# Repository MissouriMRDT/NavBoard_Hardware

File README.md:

# MRDT NavBoard Hardware

## Purpose
The Navigation (Nav) Board is responsible for containing, supplying, and interfacing the equipment required to determine the rover's position and orientation. This board does this by utilizing 2 inertial measurement units (IMUs) and a connection to an external GPS receiver. This data is processed and sent to the rest of the rover via an ethernet connection.
## Design

This revision of the board is a new design, based on the components and connections from the 2022/2023 Rev 2 designs. The goal of this design was to make the board as small as possible, and to mount onto a Teensy 4.1 instead of a raspberry pi.

This design utilizes a 4-layer PCB with holes for M3 mounting screws on 15mm standoffs. The Teensy is soldered onto one side of the board, and all of the smd components are mounted on the other side.

This design also includes an ethernet RJ45 jack for allowing ethernet connectivity to the Teensy.

## Required External Connections
 - +12V
 - GPS (I2C and UART)
 - Teensy 4.1
 - Ethernet

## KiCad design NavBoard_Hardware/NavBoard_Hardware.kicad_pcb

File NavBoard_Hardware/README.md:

# MRDT NavBoard PCB

## Dimensions
 - 100mm Long (124.29mm w/ Horizontal Power Poles)
 - 33.1mm Wide
## Board Specifications

 - 4-layer
  -- Top Copper (Signals, SMD Components, Ground Pour)
  -- Ground Copper
  -- Power Copper (3V3, 5V, 12V)
  -- Bottom Copper (Signals, Ethernet, Ground Pour)
 - 1-oz Copper
 - 1.6mm Thick
## Mounting Points
This module is designed as a daughter board to be mounted on top of a Teensy 4.1 microcontroller. There are holes at each corner of the board for mounting M3 standoffs. These holes are electrically connected to ground.

The powerpole connectors can be mounted vertically to reduce horizontal space.

The Teensy 4.1 needs to be mounted with the USB port facing the Ethernet port.

The Teensy 4.1 also needs to be mounted so that its reset button is accessible.

The MicroSD card should be accessible if the PowerPole connectors do not extend below the holes too much.

The Teensy 4.1 ethernet pins are 2.00mm pitch, NOT the standard 2.54mm. These also will likely need to be longer than standard 2.00mm pins, as 2.00 pins are shorter in length an 2.54mm pins.

The Teensy 4.1 CAN be socketed onto the PCB, but it is recommended for structural integrity reasons that it be direcly soldered into place using 2.54mm and 2.00mm pins.

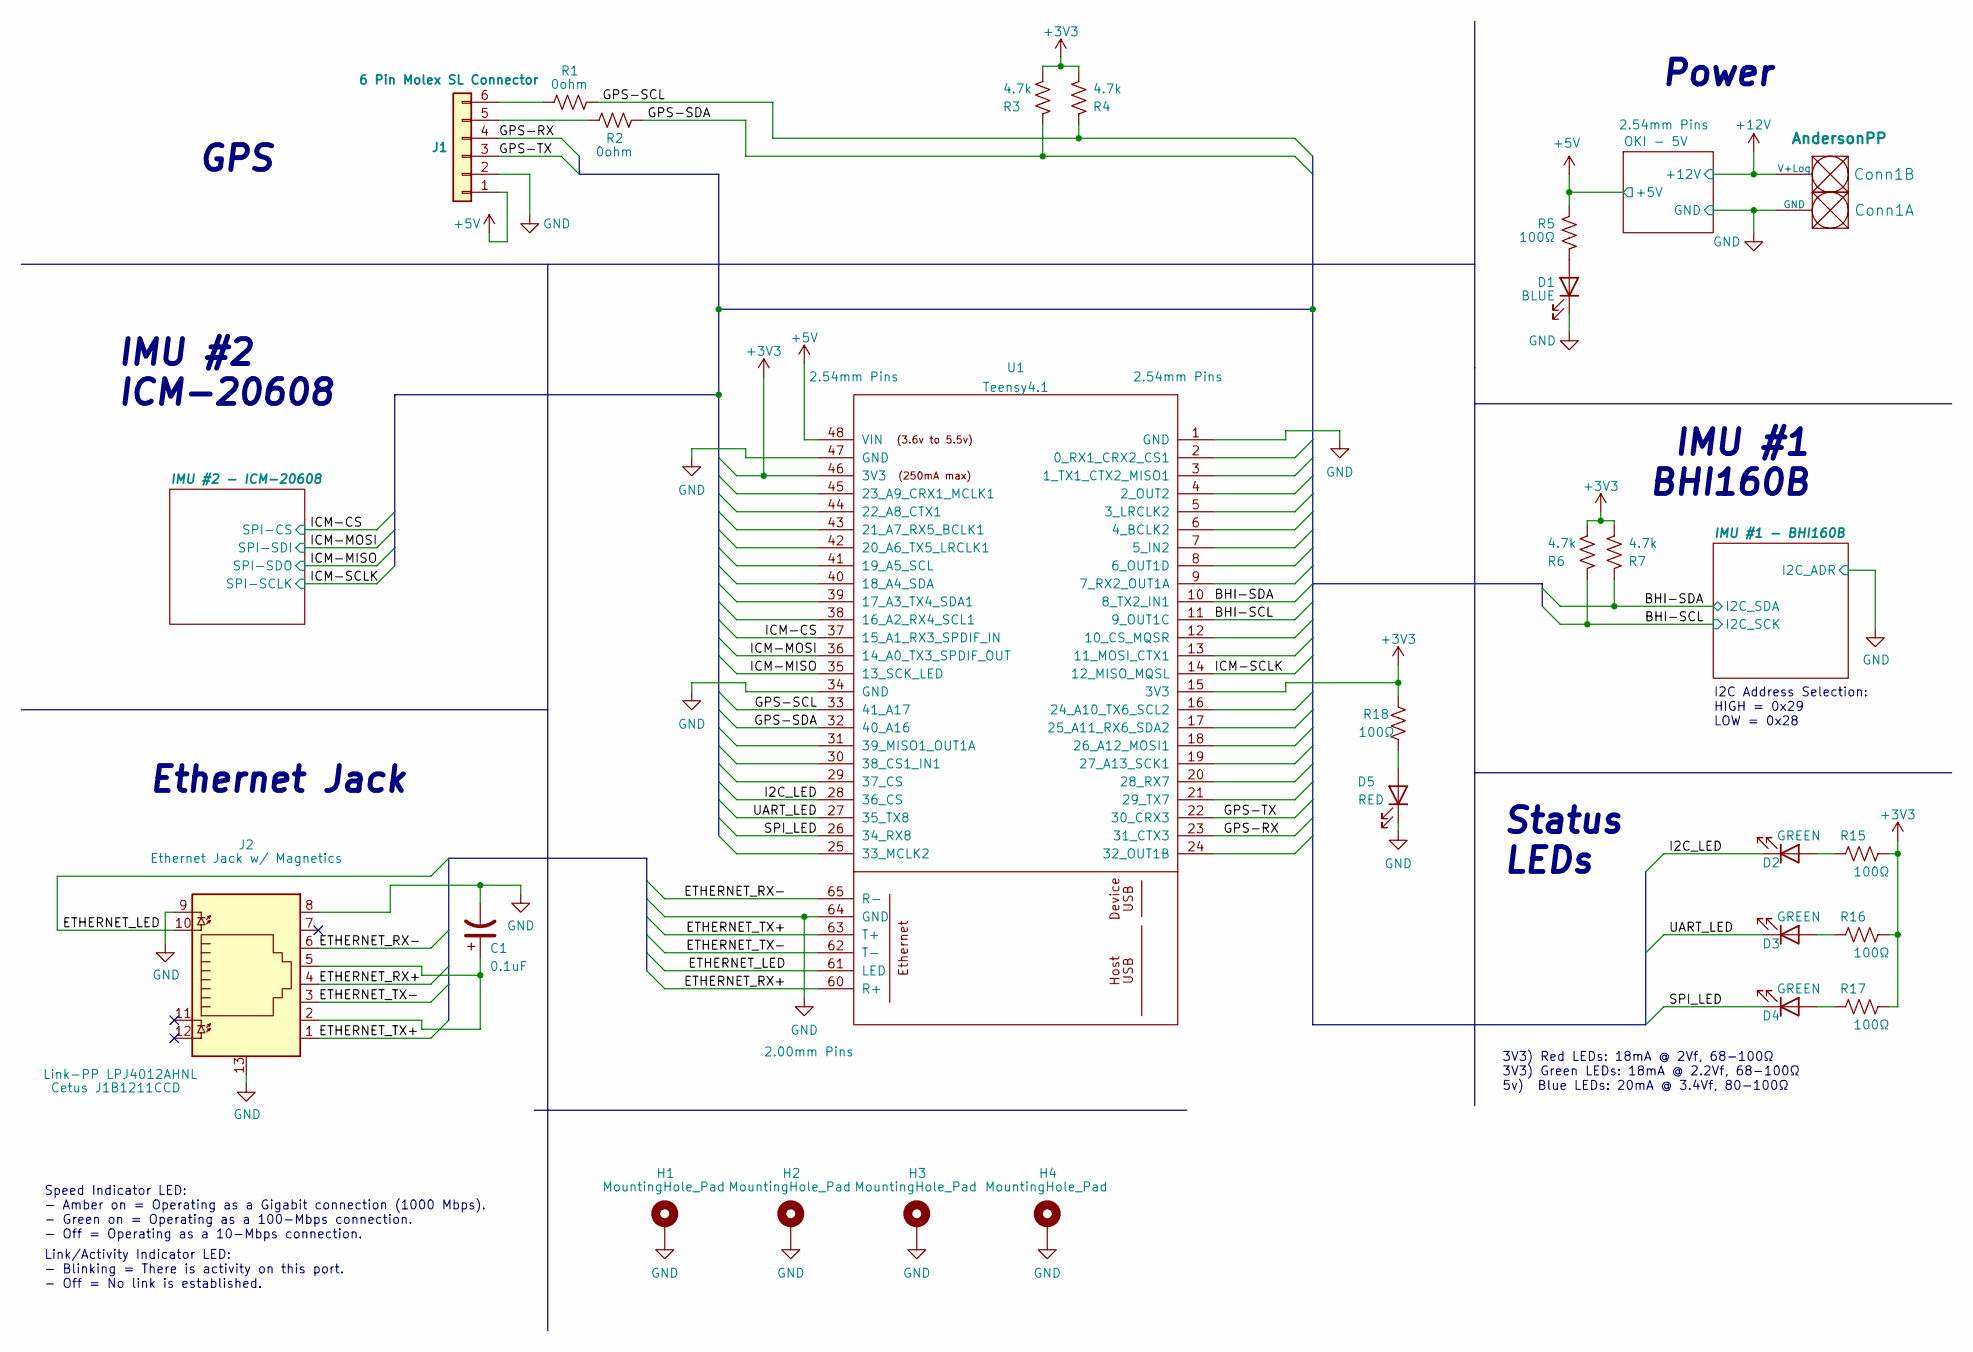
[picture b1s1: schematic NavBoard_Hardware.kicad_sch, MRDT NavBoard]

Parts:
C1: 0.1uF; C_0603_1608Metric_Pad1.08x0.95mm_HandSolder
Conn1: AndersonPP; Square_Anderson_2_H_Side_By_Side
D1: BLUE; LED_0603_1608Metric_Pad1.05x0.95mm_HandSolder
D2, D3, D4: GREEN; LED_0603_1608Metric_Pad1.05x0.95mm_HandSolder
D5: RED; LED_0603_1608Metric_Pad1.05x0.95mm_HandSolder
H1, H2, H3, H4: MountingHole_Pad
J1: 6 Pin Molex SL Connector; MOLEX_SL_06_Vertical
J2: Ethernet Jack w/ Magnetics; RJ45_Cetus_J1B1211CCD_Horizontal; Part Opt 1 Link-PP LPJ4012AHNL
R1, R2: 0ohm; R_0603_1608Metric_Pad0.98x0.95mm_HandSolder
R3, R4, R6, R7: 4.7k; R_0603_1608Metric_Pad0.98x0.95mm_HandSolder
R5, R15, R16, R17, R18: 100Ω; R_0603_1608Metric_Pad0.98x0.95mm_HandSolder
U1: Teensy4.1; Teensy41

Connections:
+5V: J1.1, R5.1, U1.48 (VIN); also elsewhere on the board
+12V: Conn1.2 (V+Log); also elsewhere on the board
/BHI-SCL: R6.1, U1.11 (9_OUT1C); also elsewhere on the board
/BHI-SDA: R7.1, U1.10 (8_TX2_IN1); also elsewhere on the board
/ETHERNET_LED: J2.10, U1.61 (LED)
/ETHERNET_RX+: J2.4, U1.60 (R+)
/ETHERNET_RX-: J2.6, U1.65 (R-)
/ETHERNET_TX+: J2.1, U1.63 (T+)
/ETHERNET_TX-: J2.3, U1.62 (T-)
/GPS-RX: J1.4, U1.23 (31_CTX3)
/GPS-SCL: R1.2, R4.1, U1.33 (41_A17)
/GPS-SDA: R2.2, R3.1, U1.32 (40_A16)
/GPS-TX: J1.3, U1.22 (30_CRX3)
/I2C_LED: D2.1 (K), U1.28 (36_CS)
/ICM-CS: U1.37 (15_A1_RX3_SPDIF_IN); also elsewhere on the board
/ICM-MISO: U1.35 (13_SCK_LED); also elsewhere on the board
/ICM-MOSI: U1.36 (14_A0_TX3_SPDIF_OUT); also elsewhere on the board
/ICM-SCLK: U1.14 (12_MISO_MQSL); also elsewhere on the board
/SPI_LED: D4.1 (K), U1.26 (34_RX8)
/UART_LED: D3.1 (K), U1.27 (35_TX8)
GND: C1.2, Conn1.1 (GND), D1.1 (K), D5.1 (K), H1.1, H2.1, H3.1, H4.1, J1.2, J2.8, J2.9, J2.13, U1.1 (GND), U1.34 (GND), U1.47 (GND), U1.64 (GND); also elsewhere on the board
unnamed: C1.1, J2.2, J2.5
unnamed: D1.2 (A), R5.2
unnamed: D2.2 (A), R15.2
unnamed: D3.2 (A), R16.2
unnamed: D4.2 (A), R17.2
unnamed: D5.2 (A), R18.2
unnamed: J1.5, R2.1
unnamed: J1.6, R1.1

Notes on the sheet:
Link/Activity Indicator LED: - Blinking = There is activity on this port. - Off = No link is established.
GPS
I2C Address Selection: HIGH = 0x29 LOW = 0x28
IMU #1 BHI160B
Status LEDs
IMU #2 ICM-20608
Speed Indicator LED: - Amber on = Operating as a Gigabit connection (1000 Mbps). - Green on = Operating as a 100-Mbps connection. - Off = Operating as a 10-Mbps connection.
Ethernet Jack
Power
3V3) Red LEDs: 18mA @ 2Vf, 68-100Ω 3V3) Green LEDs: 18mA @ 2.2Vf, 68-100Ω 5v) Blue LEDs: 20mA @ 3.4Vf, 80-100Ω

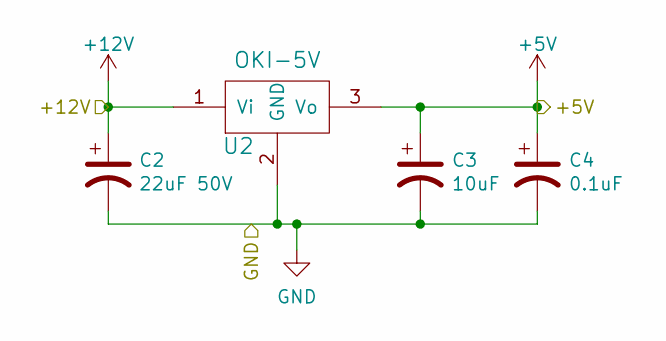
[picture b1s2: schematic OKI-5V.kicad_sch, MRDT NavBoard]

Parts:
C2: 22uF 50V; C_1206_3216Metric_Pad1.33x1.80mm_HandSolder
C3: 10uF; C_0603_1608Metric_Pad1.08x0.95mm_HandSolder
C4: 0.1uF; C_0603_1608Metric_Pad1.08x0.95mm_HandSolder
U2: OKI-5V; OKI_Vertical_TSR

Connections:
+5V: C3.1, C4.1, U2.3 (Vo); also elsewhere on the board
+12V: C2.1, U2.1 (Vi); also elsewhere on the board
GND: C2.2, C3.2, C4.2, U2.2 (GND); also elsewhere on the board

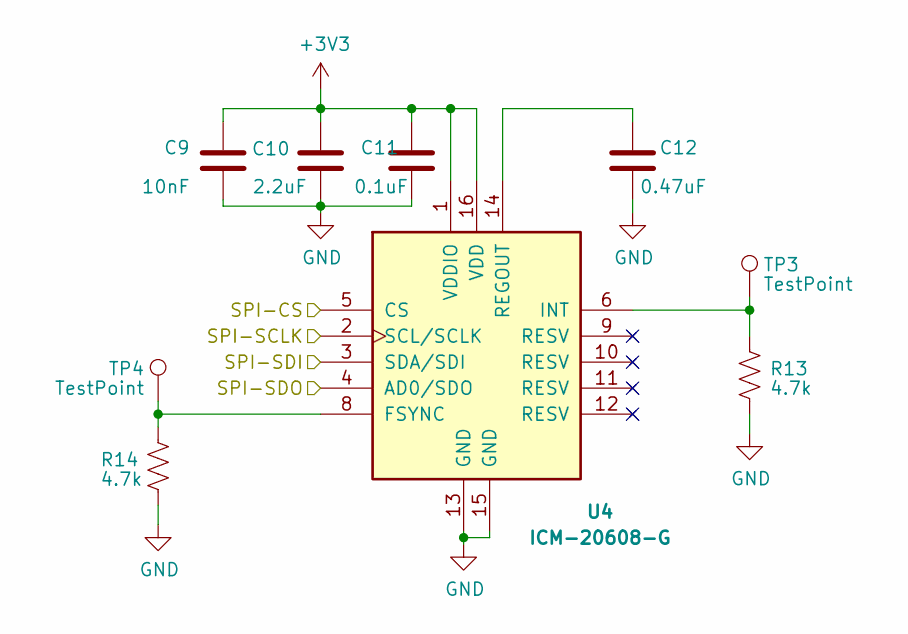
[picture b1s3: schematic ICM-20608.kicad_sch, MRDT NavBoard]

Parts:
C9: 10nF; C_0603_1608Metric_Pad1.08x0.95mm_HandSolder
C10: 2.2uF; C_0603_1608Metric_Pad1.08x0.95mm_HandSolder
C11: 0.1uF; C_0603_1608Metric_Pad1.08x0.95mm_HandSolder
C12: 0.47uF; C_0603_1608Metric_Pad1.08x0.95mm_HandSolder
R13, R14: 4.7k; R_0603_1608Metric_Pad0.98x0.95mm_HandSolder
TP3, TP4: TestPoint; TestPoint_Pad_D1.5mm
U4: ICM-20608-G; ICM-20608-G_ExtendedPads; PARTREV 1.0

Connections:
/ICM-CS: U4.5 (CS); also elsewhere on the board
/ICM-MISO: U4.4 (AD0/SDO); also elsewhere on the board
/ICM-MOSI: U4.3 (SDA/SDI); also elsewhere on the board
/ICM-SCLK: U4.2 (SCL/SCLK); also elsewhere on the board
GND: C9.2, C10.2, C11.2, C12.2, R13.2, R14.2, U4.13 (GND), U4.15 (GND); also elsewhere on the board
unnamed: C12.1, U4.14 (REGOUT)
unnamed: R13.1, TP3.1, U4.6 (INT)
unnamed: R14.1, TP4.1, U4.8 (FSYNC)

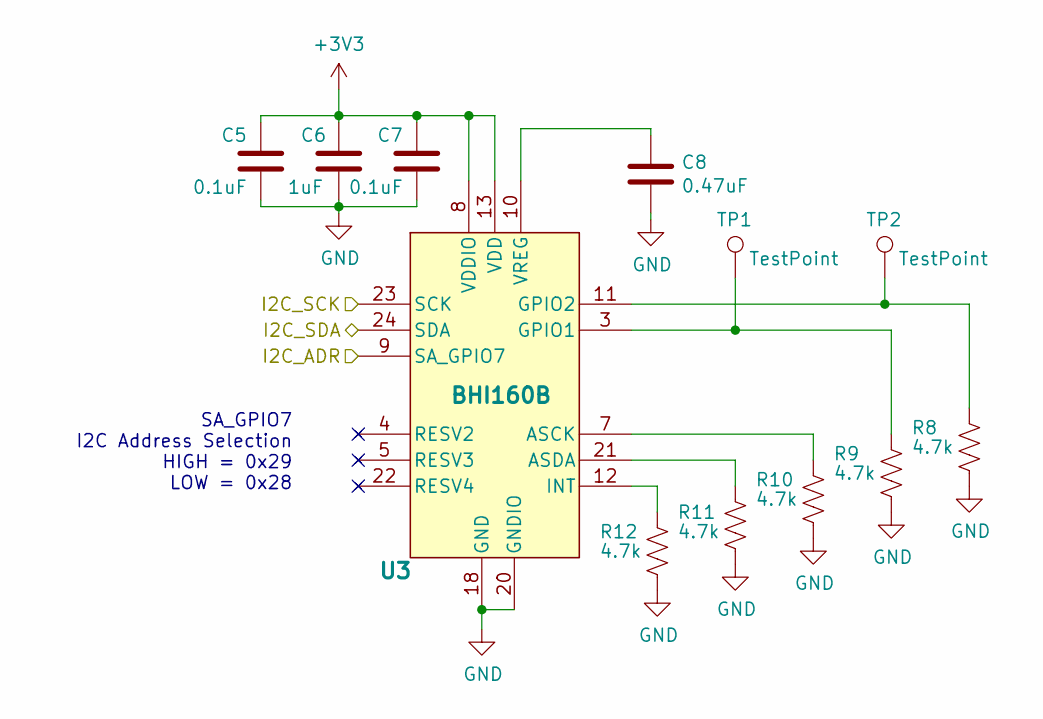
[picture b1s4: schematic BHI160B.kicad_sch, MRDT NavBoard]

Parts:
C5, C7: 0.1uF; C_0603_1608Metric_Pad1.08x0.95mm_HandSolder
C6: 1uF; C_0603_1608Metric_Pad1.08x0.95mm_HandSolder
C8: 0.47uF; C_0603_1608Metric_Pad1.08x0.95mm_HandSolder
R8, R9, R10, R11, R12: 4.7k; R_0603_1608Metric_Pad0.98x0.95mm_HandSolder
TP1, TP2: TestPoint; TestPoint_Pad_D1.5mm
U3: BHI160B; BHI160B_ExtendedPads

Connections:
/BHI-SCL: U3.23 (SCK); also elsewhere on the board
/BHI-SDA: U3.24 (SDA); also elsewhere on the board
GND: C5.2, C6.2, C7.2, C8.2, R8.2, R9.2, R10.2, R11.2, R12.2, U3.9 (SA_GPIO7), U3.18 (GND), U3.20 (GNDIO); also elsewhere on the board
unnamed: C8.1, U3.10 (VREG)
unnamed: R8.1, TP2.1, U3.11 (GPIO2)
unnamed: R9.1, TP1.1, U3.3 (GPIO1)
unnamed: R10.1, U3.7 (ASCK)
unnamed: R11.1, U3.21 (ASDA)
unnamed: R12.1, U3.12 (INT)

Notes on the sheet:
SA_GPIO7 I2C Address Selection HIGH = 0x29 LOW = 0x28

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
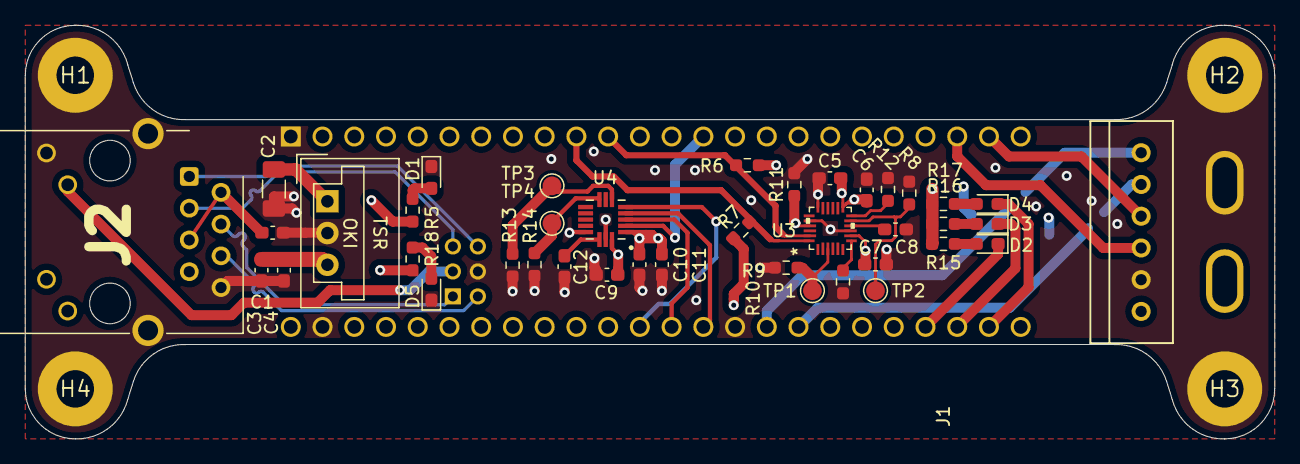
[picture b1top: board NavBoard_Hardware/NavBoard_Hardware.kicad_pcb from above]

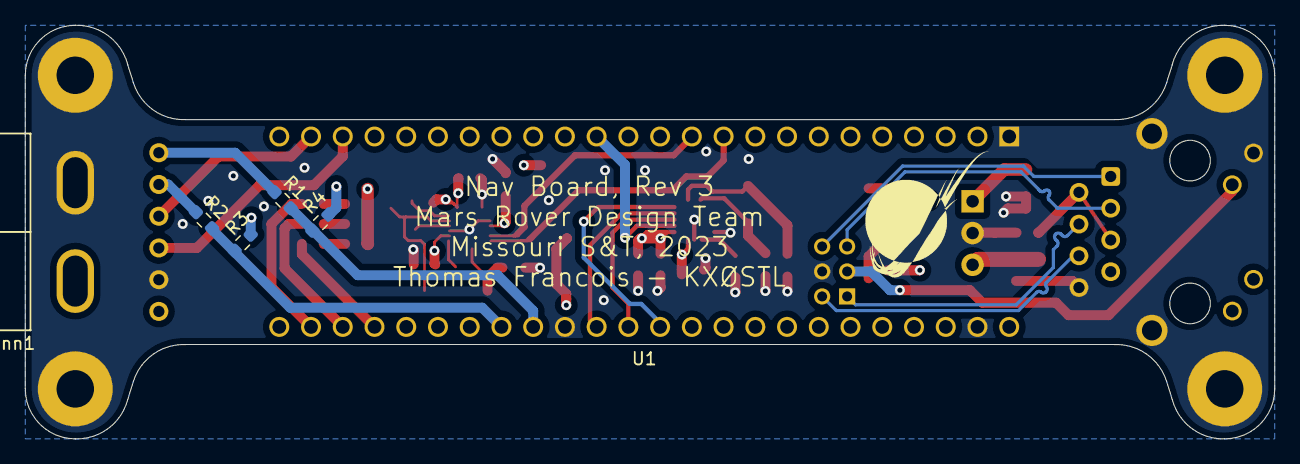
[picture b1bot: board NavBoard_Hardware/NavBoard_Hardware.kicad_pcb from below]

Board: 4 copper layers, 100.0 x 33.1 mm, 50 parts (6 on the bottom side), 39 nets.

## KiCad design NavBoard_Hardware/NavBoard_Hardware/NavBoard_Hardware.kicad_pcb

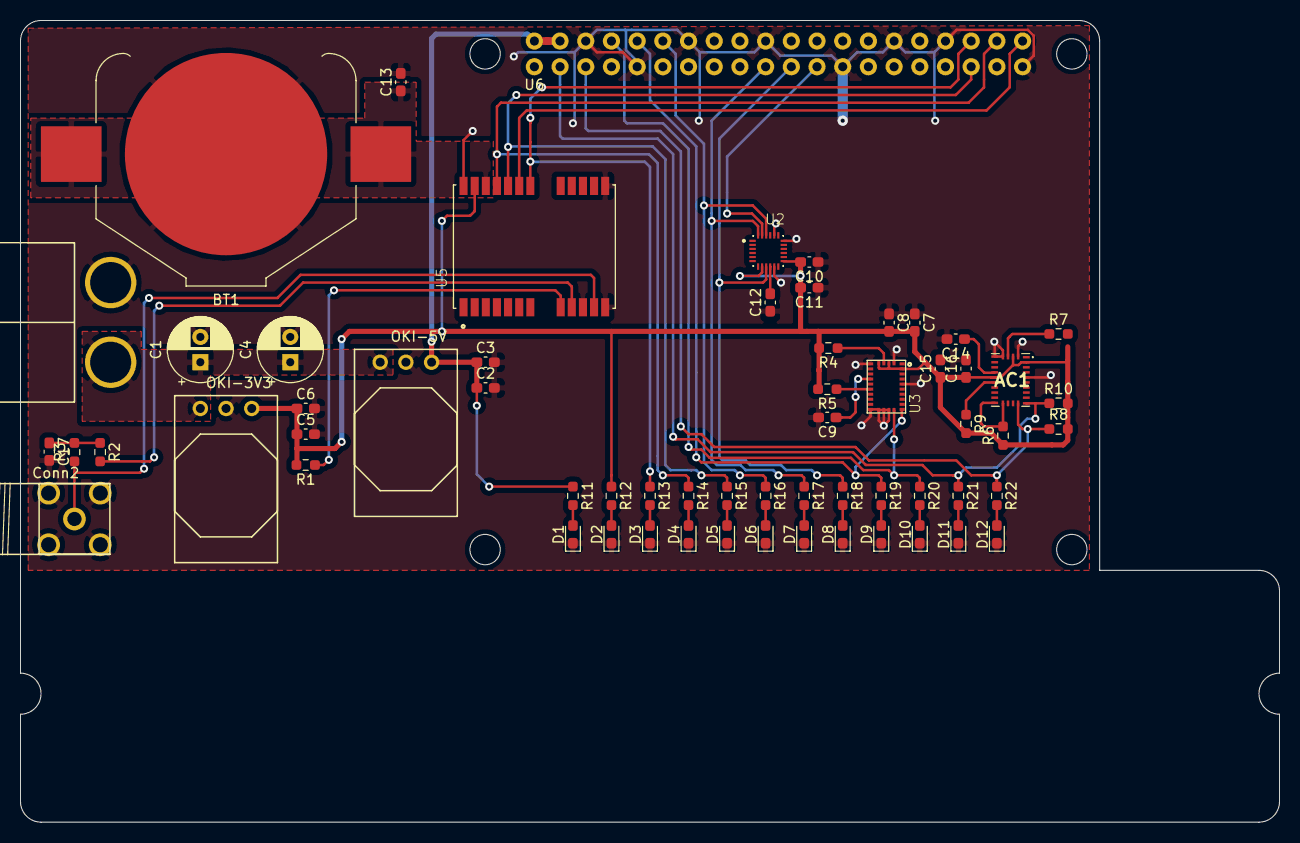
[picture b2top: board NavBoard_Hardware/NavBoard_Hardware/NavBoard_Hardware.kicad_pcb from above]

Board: 2 copper layers, 124.5 x 79.2 mm, 61 parts (0 on the bottom side), 41 nets.

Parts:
AC1: BNO080
BT1: Battery_Cell; BatteryHolder_Keystone_3008_1x2450
C1, C4: 22uF 50V; CP_Radial_D6.3mm_P2.50mm
C2, C5: 10uF; C_0603_1608Metric_Pad1.08x0.95mm_HandSolder
C3, C6, C9, C10, C11, C12, C14, C15, C16: 0.1uF; C_0603_1608Metric_Pad1.08x0.95mm_HandSolder
C7: 6.8nF; C_0603_1608Metric_Pad1.08x0.95mm_HandSolder
C8: 120nF; C_0603_1608Metric_Pad1.08x0.95mm_HandSolder
C13: 1uF; C_0603_1608Metric_Pad1.08x0.95mm_HandSolder
C17: 47pF; C_0603_1608Metric_Pad1.08x0.95mm_HandSolder
Conn1: AndersonPP; Anderson_2_Horizontal_Side_by_Side
Conn2: RP-SMA; RP-SMA_Jack_Tru-Hole_Right-Angle
D1, D2: GREEN; LED_0603_1608Metric_Pad1.05x0.95mm_HandSolder
D3, D4, D5, D6, D7, D8, D9, D10, D11, D12: BLUE; LED_0603_1608Metric_Pad1.05x0.95mm_HandSolder
R1: 10K; R_0603_1608Metric_Pad0.98x0.95mm_HandSolder
R2: 10; R_0603_1608Metric_Pad0.98x0.95mm_HandSolder
R3: 30@100MHZ/2.0A; R_0603_1608Metric_Pad0.98x0.95mm_HandSolder
R4, R5, R7, R9: 10k; R_0603_1608Metric_Pad0.98x0.95mm_HandSolder
R6, R8, R10: 2.2k; R_0603_1608Metric_Pad0.98x0.95mm_HandSolder
R11, R13, R14, R15, R16, R17, R18, R19, R20, R21, R22: 100; R_0603_1608Metric_Pad0.98x0.95mm_HandSolder
R12: 43; R_0603_1608Metric_Pad0.98x0.95mm_HandSolder
U1: OKI-5V; OKI_Horizontal
U2: ICM-20948; ICM_20948
U3: BNO055
U4: OKI-3V3; OKI_Horizontal
U5: NEO-M8P-2; MODULE_NEO-M8P-2
U6: Raspberry_Pi; RaspberryPi_THT_BOTTOM

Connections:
+3V3: AC1.3, AC1.10, AC1.28, C5.1, C6.1, C7.2, C8.2, C10.2, C11.2, C15.1, C16.1, R1.2, R4.2, R5.2, R6.1, R7.2, R8.2, R9.2, R10.2, R12.1, U2.8, U2.13, U3.3, U3.5, U3.28, U4.3, U5.23
+5V: C2.1, C3.1, R11.1, U1.3, U6.2, U6.4
+12V: C1.1, C4.1, Conn1.2, U1.1, U4.1
BNO055_RX: R20.1, U3.19, U6.8
BNO055_TX: R19.1, U3.20, U6.10
BNO080_SCL: AC1.19, R8.1, R22.1, U6.5
BNO080_SDA: AC1.20, R10.1, R21.1, U6.3
GND: AC1.2, AC1.5, AC1.6, AC1.25, BT1.2, C1.2, C2.2, C3.2, C4.2, C5.2, C6.2, C7.1, C8.1, C9.2, C10.1, C11.1, C12.1, C13.2, C14.2, C15.2, C16.2, C17.2, Conn1.1, Conn2.2, D1.1, D2.1, D3.1, D4.1, D5.1, D6.1, D7.1, D8.1, D9.1, D10.1, D11.1, D12.1, U1.2, U2.11, U2.18, U2.20, U3.2, U3.6, U3.15, U3.16, U3.17, U3.18, U3.25, U4.2, U5.2, U5.10, U5.12, U5.13, U5.24, U6.6, U6.9, U6.14, U6.20, U6.25, U6.30, U6.34, U6.39
ICM_CS: R16.1, U2.22, U6.12
ICM_MISO: R18.1, U2.9, U6.21
ICM_MOSI: R17.1, U2.24, U6.19
ICM_SCLK: U2.23, U6.23
M8P_CLK: U5.19, U6.40
M8P_CS: R13.1, U5.18, U6.36
M8P_MISO: R15.1, U5.20, U6.35
M8P_MOSI: R14.1, U5.21, U6.38
unnamed: AC1.4, R7.1
unnamed: AC1.9, C14.1
unnamed: AC1.11, R9.1
unnamed: AC1.15, AC1.16, R6.2
unnamed: C9.1, U3.9
unnamed: C12.2, U2.10
unnamed: C17.1, R2.1, R3.2
unnamed: Conn2.1, R3.1, U5.11
unnamed: D1.2, R11.2
unnamed: D2.2, R12.2
unnamed: D3.2, R13.2
unnamed: D4.2, R14.2
unnamed: D5.2, R15.2
unnamed: D6.2, R16.2
unnamed: D7.2, R17.2
unnamed: D8.2, R18.2
unnamed: D9.2, R19.2
unnamed: D10.2, R20.2
unnamed: D11.2, R21.2
unnamed: D12.2, R22.2
unnamed: R1.1, U5.8
unnamed: R2.2, U5.9
unnamed: R4.1, U3.4
unnamed: R5.1, U3.11
V_BCKP: BT1.1, C13.1, U5.22

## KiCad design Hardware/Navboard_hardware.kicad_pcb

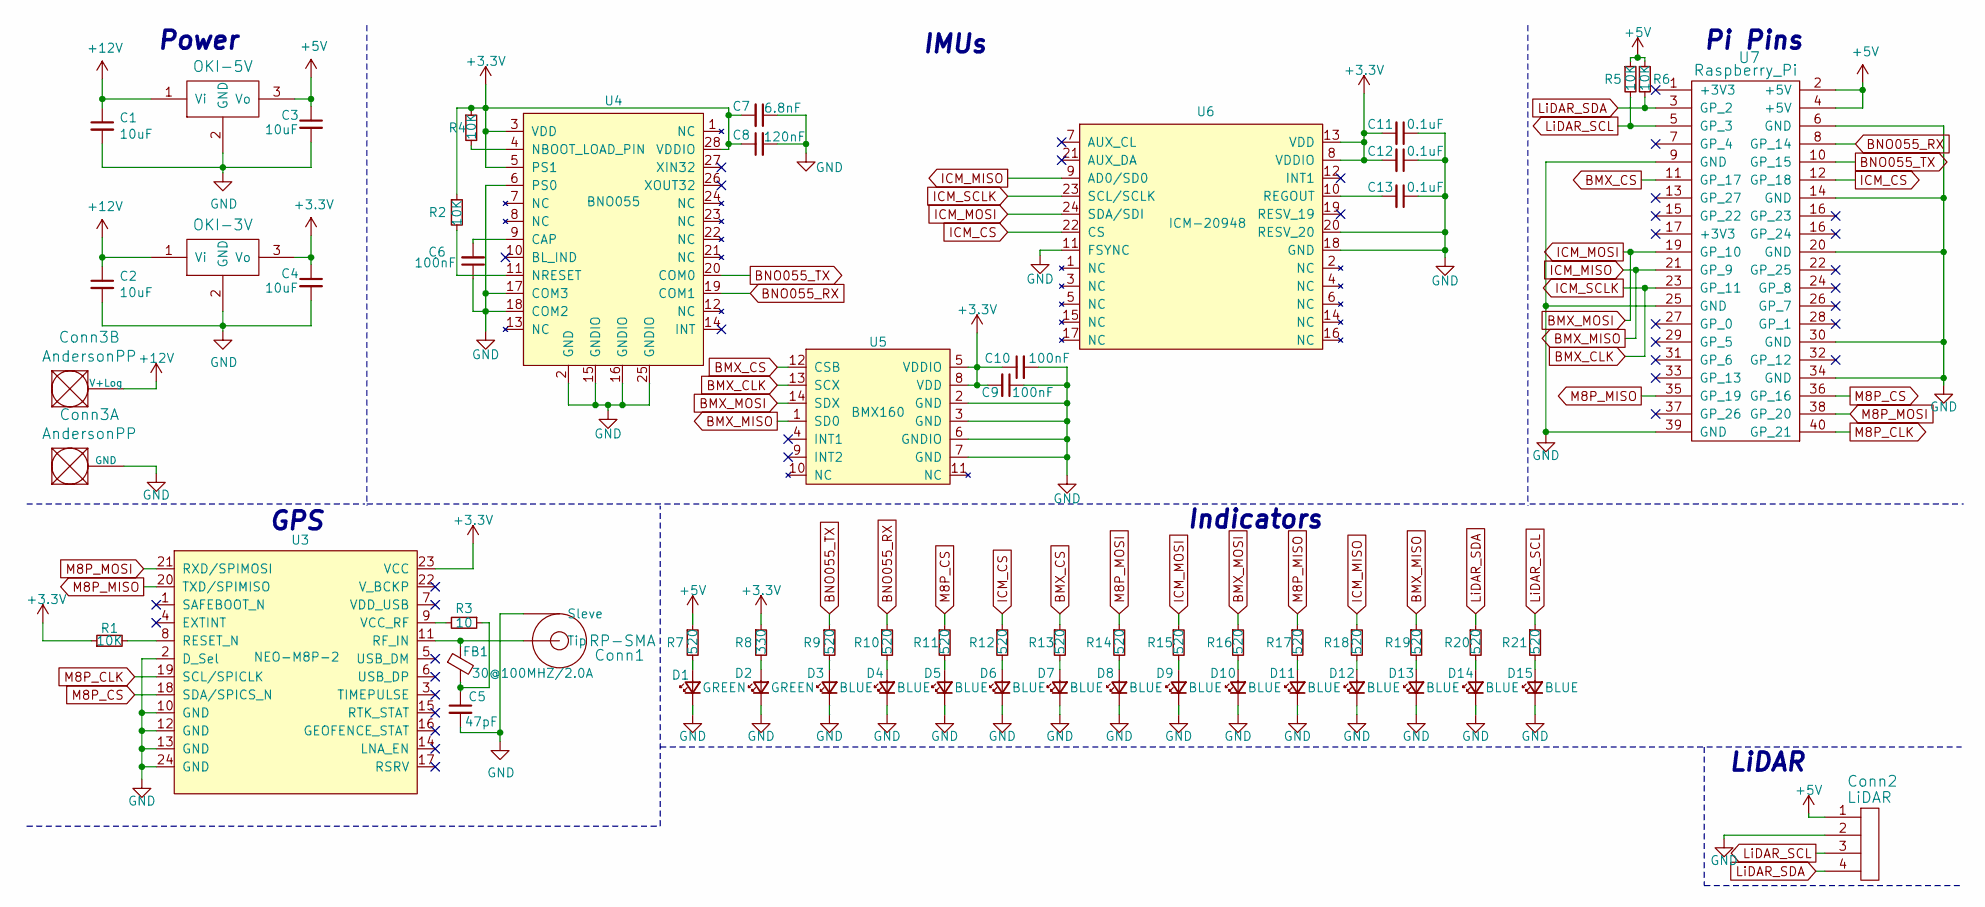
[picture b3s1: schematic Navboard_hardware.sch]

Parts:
C1, C2, C3, C4: 10uF; C_0603_1608Metric_Pad1.08x0.95mm_HandSolder
C5: 47pF; C_0603_1608Metric_Pad1.08x0.95mm_HandSolder
C6, C9, C10: 100nF; C_0603_1608Metric_Pad1.08x0.95mm_HandSolder
C7: 6.8nF; C_0603_1608Metric_Pad1.08x0.95mm_HandSolder
C8: 120nF; C_0603_1608Metric_Pad1.08x0.95mm_HandSolder
C11, C12, C13: 0.1uF; C_0603_1608Metric_Pad1.08x0.95mm_HandSolder
Conn1: RP-SMA; RP-SMA_Jack_Tru-Hole_Right-Angle
Conn2: LiDAR; MOLEX_SL_04_Horizontal
Conn3: AndersonPP; Anderson_2_Horizontal_Side_by_Side
D1, D2: GREEN; LED_0603_1608Metric_Pad1.05x0.95mm_HandSolder
D3, D4, D5, D6, D7, D8, D9, D10, D11, D12, D13, D14, D15: BLUE; LED_0603_1608Metric_Pad1.05x0.95mm_HandSolder
FB1: 30@100MHZ/2.0A; R_0603_1608Metric_Pad0.98x0.95mm_HandSolder
R1, R2, R4, R5, R6: 10K; R_0603_1608Metric_Pad0.98x0.95mm_HandSolder
R3: 10; R_0603_1608Metric_Pad0.98x0.95mm_HandSolder
R7, R9, R10, R11, R12, R13, R14, R15, R16, R17, R18, R19, R20, R21: 520; R_0603_1608Metric_Pad0.98x0.95mm_HandSolder
R8: 330; R_0603_1608Metric_Pad0.98x0.95mm_HandSolder
U1: OKI-5V; OKI_Horizontal
U2: OKI-3V; OKI_Horizontal
U3: NEO-M8P-2; MODULE_NEO-M8P-2
U4: BNO055
U5: BMX160
U6: ICM-20948; ICM_20948
U7: Raspberry_Pi; RaspberryPi_THT_BOTTOM

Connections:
+3V3: C4.1, C7.2, C8.1, C9.2, C10.1, C11.2, C12.2, R1.1, R2.1, R4.1, R8.1, U2.3 (Vo), U3.23 (VCC), U4.3 (VDD), U4.5 (PS1), U4.28 (VDDIO), U5.5 (VDDIO), U5.8 (VDD), U6.8 (VDDIO), U6.13 (VDD)
+5V: C3.1, Conn2.1, R5.1, R6.1, R7.1, U1.3 (Vo), U7.2 (+5V), U7.4 (+5V)
+12V: C1.1, C2.1, Conn3.2 (V+Log), U1.1 (Vi), U2.1 (Vi)
BMX_CLK: U5.13 (SCX), U6.23 (SCL/SCLK), U7.23 (GP_11)
BMX_CS: R13.1, U5.12 (CSB), U7.11 (GP_17)
BMX_MISO: R18.1, R19.1, U5.1 (SD0), U6.9 (AD0/SD0), U7.21 (GP_9)
BMX_MOSI: R15.1, R16.1, U5.14 (SDX), U6.24 (SDA/SDI), U7.19 (GP_10)
BNO055_RX: R10.1, U4.19 (COM1), U7.8 (GP_14)
BNO055_TX: R9.1, U4.20 (COM0), U7.10 (GP_15)
GND: C1.2, C2.2, C3.2, C4.2, C5.2, C6.1, C7.1, C8.2, C9.1, C10.2, C11.1, C12.1, C13.1, Conn1.2 (Sleve), Conn2.2, Conn3.1 (GND), D1.1 (K), D2.1 (K), D3.1 (K), D4.1 (K), D5.1 (K), D6.1 (K), D7.1 (K), D8.1 (K), D9.1 (K), D10.1 (K), D11.1 (K), D12.1 (K), D13.1 (K), D14.1 (K), D15.1 (K), U1.2 (GND), U2.2 (GND), U3.2 (D_Sel), U3.10 (GND), U3.12 (GND), U3.13 (GND), U3.24 (GND), U4.2 (GND), U4.6 (PS0), U4.15 (GNDIO), U4.16 (GNDIO), U4.17 (COM3), U4.18 (COM2), U4.25 (GNDIO), U5.2 (GND), U5.3 (GND), U5.6 (GNDIO), U5.7 (GND), U6.11 (FSYNC), U6.18 (GND), U6.20 (RESV_20), U7.6 (GND), U7.9 (GND), U7.14 (GND), U7.20 (GND), U7.25 (GND), U7.30 (GND), U7.34 (GND), U7.39 (GND); also elsewhere on the board
ICM_CS: R12.1, U6.22 (CS), U7.12 (GP_18)
LiDAR_SCL: Conn2.3, R5.2, R21.1, U7.5 (GP_3)
LiDAR_SDA: Conn2.4, R6.2, R20.1, U7.3 (GP_2)
M8P_CLK: U3.19 (SCL/SPICLK), U7.40 (GP_21)
M8P_CS: R11.1, U3.18 (SDA/SPICS_N), U7.36 (GP_16)
M8P_MISO: R17.1, U3.20 (TXD/SPIMISO), U7.35 (GP_19)
M8P_MOSI: R14.1, U3.21 (RXD/SPIMOSI), U7.38 (GP_20)
unnamed: C5.1, FB1.2, R3.1
unnamed: C6.2, U4.9 (CAP)
unnamed: C13.2, U6.10 (REGOUT)
unnamed 20: Conn1.1 (Tip), FB1.1, U3.11 (RF_IN); also elsewhere on the board
unnamed: D1.2 (A), R7.2
unnamed: D2.2 (A), R8.2
unnamed: D3.2 (A), R9.2
unnamed: D4.2 (A), R10.2
unnamed: D5.2 (A), R11.2
unnamed: D6.2 (A), R12.2
unnamed: D7.2 (A), R13.2
unnamed: D8.2 (A), R14.2
unnamed: D9.2 (A), R15.2
unnamed: D10.2 (A), R16.2
unnamed: D11.2 (A), R17.2
unnamed: D12.2 (A), R18.2
unnamed: D13.2 (A), R19.2
unnamed: D14.2 (A), R20.2
unnamed: D15.2 (A), R21.2
unnamed: R1.2, U3.8 (RESET_N)
unnamed: R2.2, U4.11 (NRESET)
unnamed: R3.2, U3.9 (VCC_RF)
unnamed: R4.2, U4.4 (NBOOT_LOAD_PIN)

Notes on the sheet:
Power
IMUs
Pi Pins
GPS
LiDAR
Indicators

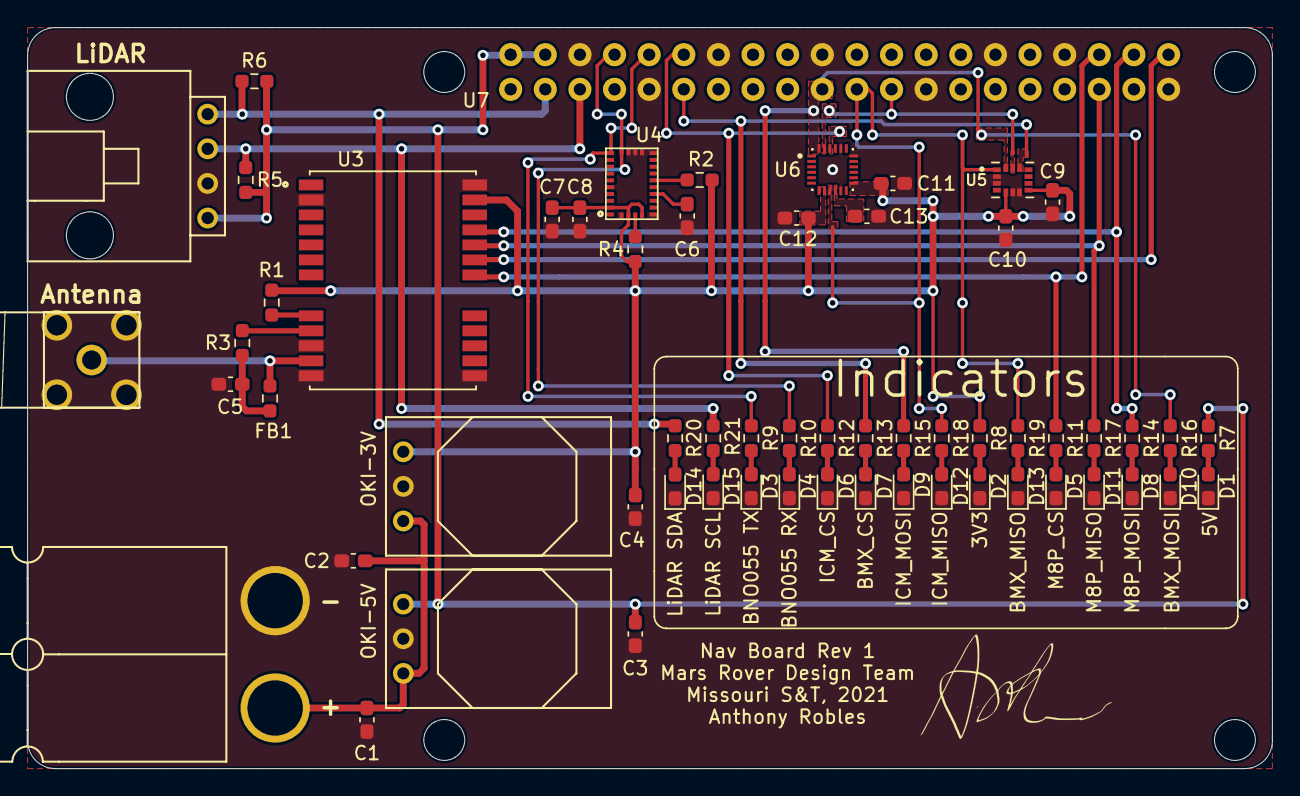
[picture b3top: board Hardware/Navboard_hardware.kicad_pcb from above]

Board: 2 copper layers, 91.3 x 54.4 mm, 60 parts (0 on the bottom side), 40 nets.

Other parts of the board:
Antenna: RP-SMA; RP-SMA_Jack_Tru-Hole_Right-Angle

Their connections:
GND: Antenna.2; also elsewhere on the board
unnamed 20: Antenna.1; also elsewhere on the board

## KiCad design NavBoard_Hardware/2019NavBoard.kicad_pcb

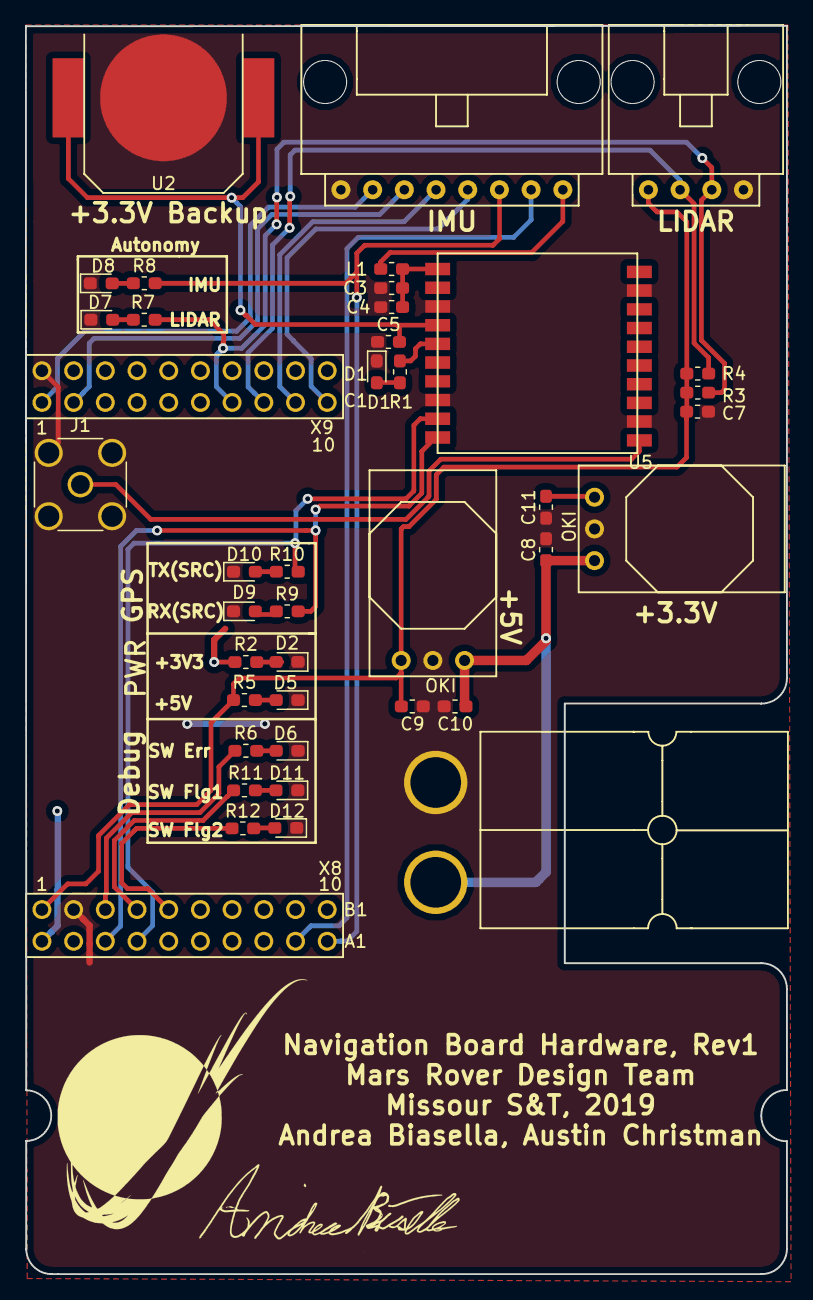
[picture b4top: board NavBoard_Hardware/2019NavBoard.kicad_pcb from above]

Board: 2 copper layers, 61.0 x 100.0 mm, 40 parts (0 on the bottom side), 31 nets.

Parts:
C3, C5: 1uF; C_0603_1608Metric_Pad1.05x0.95mm_HandSolder
C4: 0.01uF; C_0603_1608Metric_Pad1.05x0.95mm_HandSolder
C7: 680uF; C_0603_1608Metric_Pad1.05x0.95mm_HandSolder
C8, C9, C10, C11: 10u; C_0603_1608Metric_Pad1.05x0.95mm_HandSolder
Conn1: AndersonPP; Anderson_2_Horisontal_Side_by_Side
Conn2: LiDAR; MOLEX_SL_04_Horizontal
Conn3: Molex_SL_08; MOLEX_SL_08_Horizontal
D1: FIX; LED_0603_1608Metric_Pad1.05x0.95mm_HandSolder
D2, D5, D6, D7, D8, D9, D10, D11, D12: PWR; LED_0603_1608Metric_Pad1.05x0.95mm_HandSolder
J1: Conn_Coaxial; SMA_Amphenol_132134-16_Vertical
L1: INDUCTOR; L_0603_1608Metric_Pad1.05x0.95mm_HandSolder
R1: 1K; R_0603_1608Metric_Pad1.05x0.95mm_HandSolder
R2, R5, R6, R7, R8, R9, R10, R11, R12: 500; R_0603_1608Metric_Pad1.05x0.95mm_HandSolder
R3, R4: 4.7K; R_0603_1608Metric_Pad1.05x0.95mm_HandSolder
U1: TM4C129E_Launchpad_X9
U2: 12mm_Coin_Battery_Cell_Holder; CR1220_Battery_Holder
U3, U4: OKI; OKI_Horizontal
U5: FGPMMOPA6H

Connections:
+3V3: C11.1, Conn3.8, L1.1, R2.1, U1.+3V3, U4.3
+5V: C7.2, C9.1, Conn2.1, R3.1, R4.2, R5.1, U1.+5V, U3.3
/EXAnt: J1.1, U5.11
DRDYM: Conn3.5, U1.PL3
Error_LED: R6.1, U1.PE0
GND: C3.1, C4.1, C5.2, C7.1, C8.2, C9.2, C10.2, C11.2, Conn1.1, Conn2.4, Conn3.1, D1.1, D2.1, D5.1, D6.1, D7.1, D8.1, D9.1, D10.1, D11.1, D12.1, J1.2, U1.GND, U2.2, U3.2, U4.2, U5.3, U5.8, U5.12, U5.19
INT1AG: Conn3.3, U1.PF2
INT2AG: Conn3.2, U1.PF1
INTM: Conn3.4, U1.PL2
LIDAR_SCL: Conn2.2, R4.1, U1.PL1
LIDAR_SDA: Conn2.3, R3.2, R7.1, U1.PL0
unnamed: C3.2, C4.2, L1.2, U5.1
unnamed: C8.1, C10.1, Conn1.2, U3.1, U4.1
unnamed: D1.2, R1.2
unnamed: D2.2, R2.2
unnamed: D5.2, R5.2
unnamed: D6.2, R6.2
unnamed: D7.2, R7.2
unnamed: D8.2, R8.2
unnamed: D9.2, R9.2
unnamed: D10.2, R10.2
unnamed: D11.2, R11.2
unnamed: D12.2, R12.2
unnamed: R1.1, U5.5
SCL(0): Conn3.7, U1.PB2
SDA(0): Conn3.6, R8.1, U1.PB3
SW_Flg1: R11.1, U1.PE1
SW_Flg2: R12.1, U1.PE2
TivaRX(7): R9.1, U1.PC4, U5.10
TivaTX(7): R10.1, U1.PC5, U5.9
VBACKUP: C5.1, U2.1, U5.4

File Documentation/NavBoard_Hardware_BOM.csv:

Id,Designator,Package,Designation,,Item Name,Part Number,,,Vendor,Quantity,Cost Per Item,,Cost,URL
1,Conn1,Anderson_2_Horisontal_Side_by_Side,AndersonPP,,Anderson Power 1336G1 Printed Circuit Board High Power 45 Amp Horizontal Bottom Contact,1336G1,,,Powerwerx,2,0.53,,,https://powerwerx.com/anderson-1336g1-printed-circuit-board-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
2,Conn1,Anderson_2_Horisontal_Side_by_Side,AndersonPP,,PP15/30/45 Loose Piece Powerpole Colored Housing,1327,,,Powerwerx,1,0.37,,,https://powerwerx.com/anderson-powerpole-colored-housings
3,Conn1,Anderson_2_Horisontal_Side_by_Side,AndersonPP,,PP15/30/45 Loose Piece Powerpole Colored Housing,1327G6,,,Powerwerx,1,0.37,,,https://powerwerx.com/anderson-powerpole-colored-housings
4,"C10,C8,C9,C11",C_0603_1608Metric_Pad1.05x0.95mm_HandSolder,10u,, CAP CER 10UF 6.3V X5R 0603,1276-1119-1-ND,,,Digikey,4,0.15,,,https://www.digikey.com/product-detail/en/samsung-electro-me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
5,"R8,R2,R5,R6,R7,R9,R10,R11,R12",R_0603_1608Metric_Pad1.05x0.95mm_HandSolder,500,,RES SMD 510 OHM 5% 1/4W 0603,RHM510DCT-ND,,,Digikey,9,0.1,,,https://www.digikey.com/product-detail/en/rohm-semiconductor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
6,"D2,D5",LED_0603_1608Metric_Pad1.05x0.95mm_HandSolder,PWR,,LED GREEN CLEAR SMD,160-1446-1-ND,,,Digikey,2,0.29,,,https://www.digikey.com/product-detail/en/lite-on-inc/LTST-C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
7,D6,LED_0603_1608Metric_Pad1.05x0.95mm_HandSolder,PWR,,LED RED CLEAR SMD,160-1447-1-ND,,,Digikey,1,0.29,,,https://www.digikey.com/product-detail/en/lite-on-inc/LTST-C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
8,"D7,D8,D9,D10",LED_0603_1608Metric_Pad1.05x0.95mm_HandSolder,PWR,,LED YELLOW CLEAR SMD,160-1448-1-ND,,,Digikey,4,0.31,,,https://www.digikey.com/product-detail/en/lite-on-inc/LTST-C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
9,"D11,D12",LED_0603_1608Metric_Pad1.05x0.95mm_HandSolder,PWR,,LED BLUE CLEAR SMD,160-1647-1-ND,,,Digikey,2,0.53,,,https://www.digikey.com/product-detail/en/lite-on-inc/LTST-C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
10,"C3,C5",C_0603_1608Metric_Pad1.05x0.95mm_HandSolder,1uF,, CAP CER 1UF 16V X7R 0603,1276-6524-1-ND,,,Digikey,2,0.1,,,https://www.digikey.com/product-detail/en/samsung-electro-me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
11,U5,FGPMMOPA6H,FGPMMOPA6H,,Ultimate GPS Module - 66 channel w/10 Hz updates - MTK3339 chipset,790,,,Adafruit,1,29.95,,,https://www.adafruit.com/product/790
12,C4,C_0603_1608Metric_Pad1.05x0.95mm_HandSolder,0.01uF,,CAP CER 10000PF 50V X7R 0603,1276-1009-1-ND,,,Digikey,1,0.1,,,https://www.digikey.com/product-detail/en/samsung-electro-me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
13,C7,C_0603_1608Metric_Pad1.05x0.95mm_HandSolder,680uF,,CAP ALUM 680UF 20% 6.3V RADIAL,1189-1438-ND,,,Digikey,1,0.29,,,https://www.digikey.com/product-detail/en/rubycon/6.3PK680ME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
14,Conn2,MOLEX_SL_04_Horizontal,LiDAR,, CONN HEADER 4POS .100 R/A GOLD,WM4902-ND,,,Digikey,1,1.16,,,https://www.digikey.com/products/en?keywords=WM4902-ND
15,Conn3,MOLEX_SL_08_Horizontal,Molex_SL_08,, CONN HEADER 7POS .100 R/A TIN,WM4159-ND,,,Digikey,1,1.25,,,https://www.digikey.com/product-detail/en/molex-connector-co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
16,D1,LED_0603_1608Metric_Pad1.05x0.95mm_HandSolder,FIX,,LED YELLOW CLEAR SMD,160-1448-1-ND,,,Digikey,1,0.31,,,https://www.digikey.com/product-detail/en/lite-on-inc/LTST-C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
17,J1,SMA_Amphenol_132134-16_Vertical,Conn_Coaxial,,CONN SMA RCPT R/A 50 OHM PCB,CONSMA002-ND,,,Digikey,1,3.61,,,https://www.digikey.com/product-detail/en/linx-technologies-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
18,L1,L_0603_1608Metric_Pad1.05x0.95mm_HandSolder,INDUCTOR,, FERRITE BEAD 600 OHM 0603 1LN,732-1593-1-ND,,,Digikey,1,0.17,,,https://www.digikey.com/product-detail/en/wurth-electronics-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
19,R1,R_0603_1608Metric_Pad1.05x0.95mm_HandSolder,1K,,RES SMD 1K OHM 5% 1/4W 0603,RHM1.0KDCT-ND,,,Digikey,1,0.1,,,https://www.digikey.com/product-detail/en/rohm-semiconductor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
20,"R3,R4",R_0603_1608Metric_Pad1.05x0.95mm_HandSolder,4.7K,, RES SMD 4.7K OHM 1% 1/8W 0603,"MCT0603-4.70K-CFCT-ND
",,,Digikey,2,0.18,,,https://www.digikey.com/product-detail/en/vishay-beyschlag/M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
21,U1,TM4C129E_Launchpad_X9,~,,EK-TM4C1294XL,296-37267-ND,,,Digikey,1,20.76,,,https://www.digikey.com/products/en?keywords=296-37267-ND
22,U1,TM4C129E_Launchpad_X9,~,,CONN HDR 20POS 0.1 GOLD PCB,S6106-ND,,,Digikey,4,1.26,,,https://www.digikey.com/product-detail/en/sullins-connector-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
23,U3,OKI_Horizontal,OKI,,DC DC CONVERTER 5V 8W ,811-2692-ND,,,Digikey,1,4.54,,,https://www.digikey.com/product-detail/en/murata-power-solut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
25,U4,OKI_Horizontal,OKI,,OKI-78SR-3.3/1.5-W36H-C,811-3014-ND,,,Digikey,1,4.54,,,https://www.digikey.com/product-detail/en/murata-power-solut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
26,Conn4,CR1220_Battery_Holder,12mm_Coin_Cell_Battery_Holder,,BATTERY RETAINER COIN 12MM SMD,36-3080-ND,,,Digikey,1,0.58,,,https://www.digikey.com/product-detail/en/keystone-electroni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
,,,,,,,,,,,,,,
27,N/A,N/A,LIDAR,,LIDAR-Lite V3hp,SEN-14599,,,Sparkfun,1,149.99,,,https://www.sparkfun.com/products/14599?gclid=Cj0KCQiA6dLgBR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

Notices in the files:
parts and their libraries:
Copyright 2021 Accelerated Designs. All rights reserved.
